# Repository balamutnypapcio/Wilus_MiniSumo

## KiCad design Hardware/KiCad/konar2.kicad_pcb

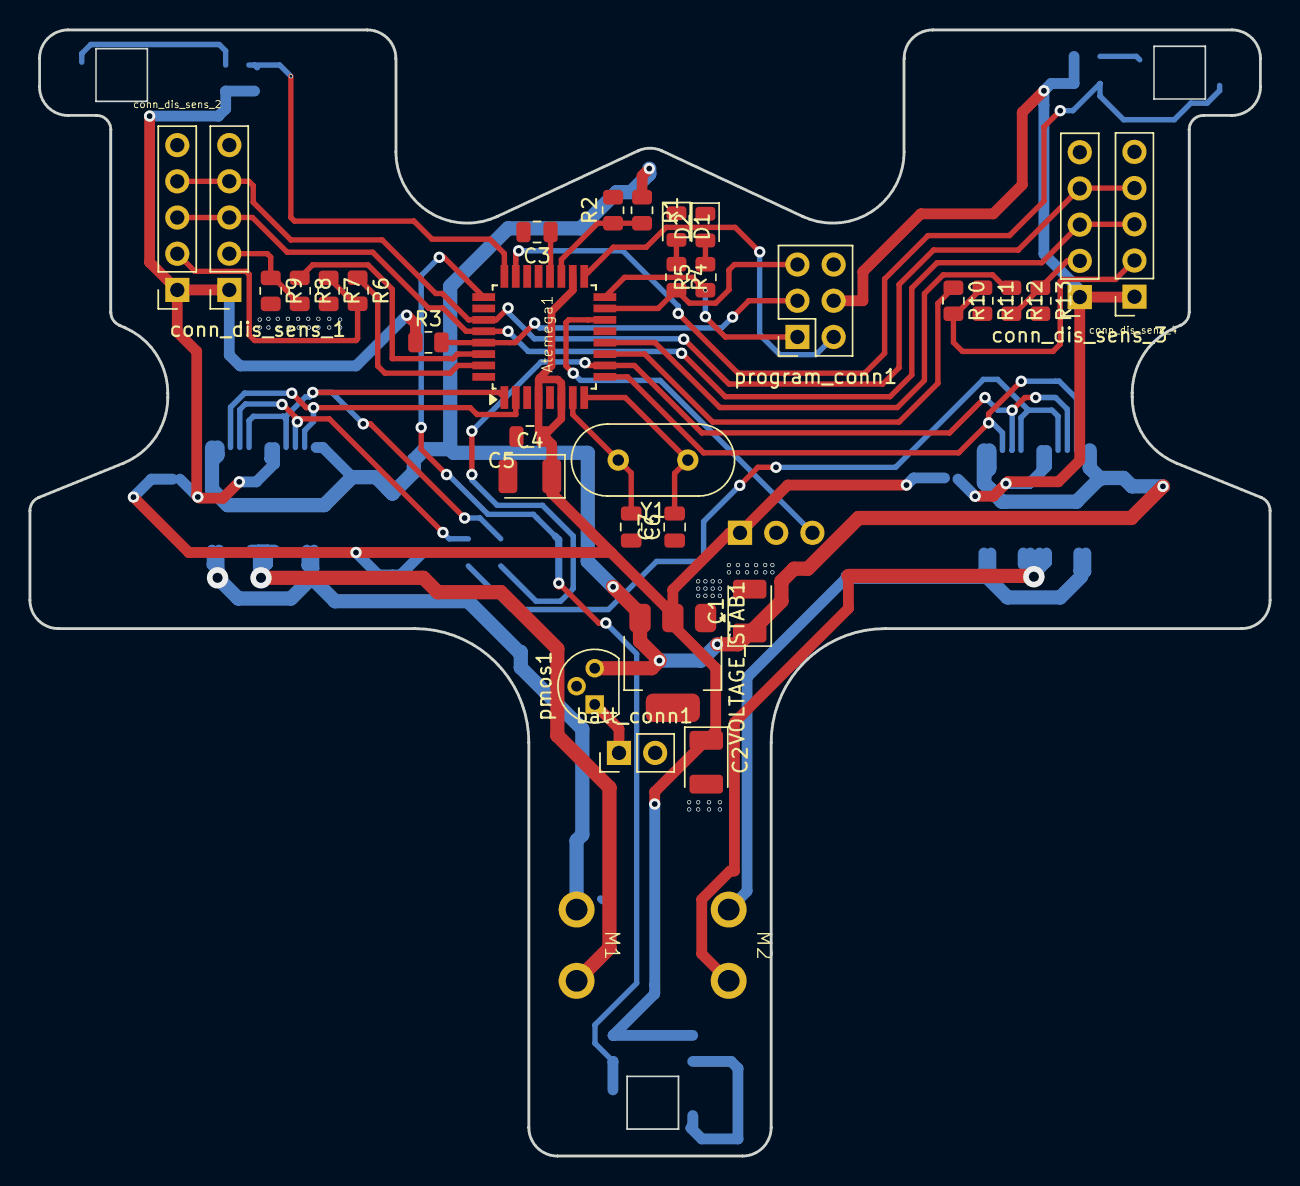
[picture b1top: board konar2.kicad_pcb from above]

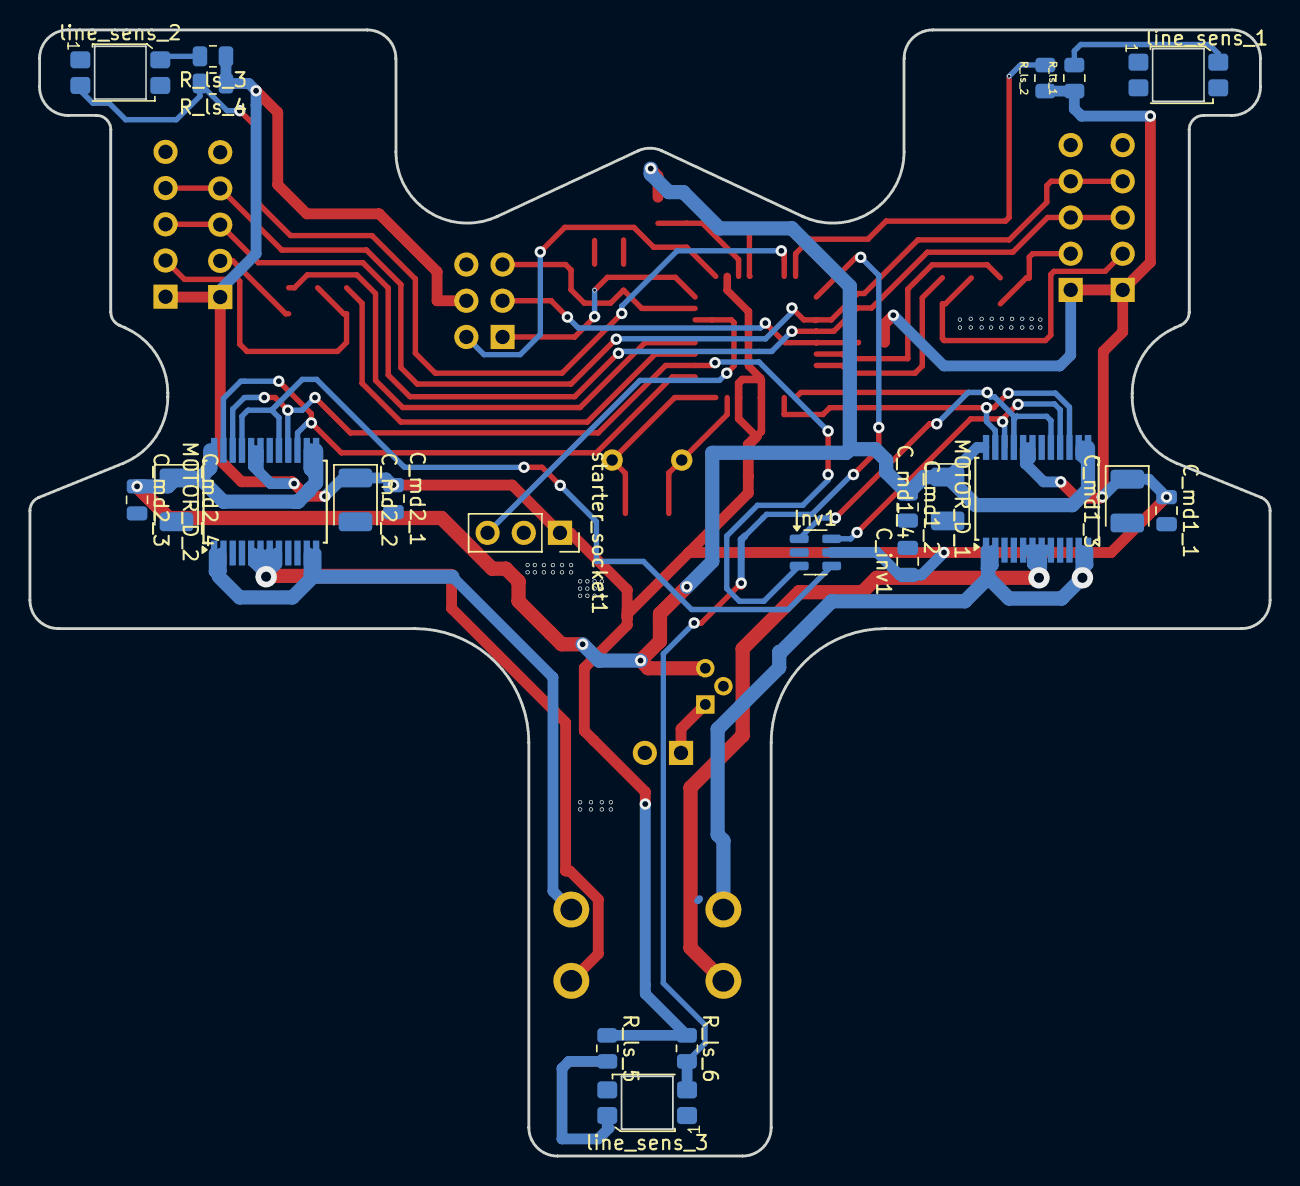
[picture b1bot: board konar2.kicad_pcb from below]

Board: 2 copper layers, 87.0 x 79.0 mm, 56 parts (22 on the bottom side), 41 nets.

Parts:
Atemega1: ATmega328P-A; TQFP-32_7x7mm_P0.8mm
C1, C2, C4: 10u; CP_EIA-3528-12_Kemet-T
C3, C5: 100n; C_0805_2012Metric
C6, C7: 22p; C_0805_2012Metric
C_inv1: 100n; C_0805_2012Metric
C_md1_1, C_md1_2, C_md2_1, C_md2_3: 100n; C_0805_2012Metric
C_md1_3, C_md1_4, C_md2_2, C_md2_4: 10u; CP_EIA-3528-12_Kemet-T
D1, D2: LED; LED_0805_2012Metric
Inv1: SN74LVC2G14DBV; SOT-23-6
M1, M2: Motor
MOTOR_D_1, MOTOR_D_2: TB6612FNG; SSOP-24_5.3x8.2mm_P0.65mm
R1, R2: 10K; R_0805_2012Metric
R3: 10k; R_0805_2012Metric
R4, R5, R6, R8, R10, R12: 1k; R_0805_2012Metric
R7, R9, R11, R13: 2k; R_0805_2012Metric
R_ls_1, R_ls_3, R_ls_5: 200R; R_0805_2012Metric
R_ls_2, R_ls_4, R_ls_6: 10k; R_0805_2012Metric
VOLTAGE_STAB1: LM1117DT-5.0; SOT-223
Y1: Crystal; Crystal_HC49-4H_Vertical
batt_conn1: Conn_01x02_Pin; PinHeader_1x02_P2.54mm_Vertical
conn_dis_sens_1, conn_dis_sens_2, conn_dis_sens_3, conn_dis_sens_4: Conn_01x05_Socket; PinSocket_1x05_P2.54mm_Vertical
line_sens_1, line_sens_2, line_sens_3: ITR8307; Everlight_ITR8307
pmos1: PMOS; TO-92L
program_conn1: AFA01-S06FCC-00; PinSocket_2x03_P2.54mm_Vertical
starter_socket1: Conn_01x03_Socket; PinSocket_1x03_P2.54mm_Vertical

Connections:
+5V: Atemega1.4 (VCC), Atemega1.6 (VCC), Atemega1.18 (AVCC), C2.1, C4.1, C5.1, C_inv1.1, C_md1_1.1, C_md1_3.1, C_md2_1.1, C_md2_2.1, Inv1.5 (V_{CC}), MOTOR_D_1.19 (STBY), MOTOR_D_1.20 (VCC), MOTOR_D_2.19 (STBY), MOTOR_D_2.20 (VCC), R3.1, R_ls_1.1, R_ls_2.1, R_ls_3.1, R_ls_4.1, R_ls_5.1, R_ls_6.1, VOLTAGE_STAB1.2 (VO), conn_dis_sens_1.1, conn_dis_sens_2.1, conn_dis_sens_3.1, conn_dis_sens_4.1, program_conn1.4, starter_socket1.1
+BATT: C1.1, C_md1_2.1, C_md1_4.1, C_md2_3.1, C_md2_4.1, MOTOR_D_1.13 (VM2), MOTOR_D_1.14 (VM3), MOTOR_D_1.24 (VM1), MOTOR_D_2.13 (VM2), MOTOR_D_2.14 (VM3), MOTOR_D_2.24 (VM1), R1.1, VOLTAGE_STAB1.3 (VI), pmos1.3 (S)
/Motor driver 1/a_2: Inv1.6 (1Y), MOTOR_D_1.16 (BIN2), MOTOR_D_1.22 (AIN2)
/Motor driver 1/ao_1: M1.1, MOTOR_D_1.1 (AO1), MOTOR_D_1.2 (AO1), MOTOR_D_1.11 (BO1), MOTOR_D_1.12 (BO1)
/Motor driver 1/ao_2: M1.2, MOTOR_D_1.5 (AO2), MOTOR_D_1.6 (AO2), MOTOR_D_1.7 (BO2), MOTOR_D_1.8 (BO2)
/Motor driver 1/pwm_1: Atemega1.2 (PD5), MOTOR_D_1.15 (PWMB), MOTOR_D_1.23 (PWMA)
/SCL: Atemega1.28 (PC5), conn_dis_sens_1.3, conn_dis_sens_2.3, conn_dis_sens_3.3, conn_dis_sens_4.3
/SDA: Atemega1.27 (PC4), conn_dis_sens_1.4, conn_dis_sens_2.4, conn_dis_sens_3.4, conn_dis_sens_4.4
/XSHUT1: R8.2, R9.1, conn_dis_sens_1.2
/XSHUT2: R6.2, R7.1, conn_dis_sens_2.2
/XSHUT3: R12.2, R13.1, conn_dis_sens_3.2
/XSHUT4: R10.2, R11.1, conn_dis_sens_4.2
/atemega/ADC7: Atemega1.19 (ADC6), R1.2, R2.1
/atemega/AREF: Atemega1.20 (AREF), C3.1
/atemega/MISO: Atemega1.16 (PB4), R5.1, program_conn1.1
/atemega/MISO_R: D2.2 (A), R5.2
/atemega/MOSI: Atemega1.15 (PB3), R4.1, program_conn1.5
/atemega/MOSI_R: D1.2 (A), R4.2
/atemega/Motor_speed_2: Atemega1.9 (PD6), MOTOR_D_2.15 (PWMB), MOTOR_D_2.23 (PWMA)
/atemega/RESET: Atemega1.29 (~RESET/PC6), R3.2, program_conn1.3
/atemega/STARTER: Atemega1.14 (PB2), starter_socket1.3
/atemega/XSHUT1: Atemega1.30 (PD1), R8.1
/atemega/XSHUT2: Atemega1.31 (PD2), R6.1
/atemega/XSHUT3: Atemega1.12 (PB0), R12.1
/atemega/XSHUT4: Atemega1.11 (PD8), R10.1
/atemega/clock: Atemega1.17 (PB5), program_conn1.2
/atemega/line_sensor_1: Atemega1.24 (PC1), R_ls_2.2, line_sens_1.3 (C)
/atemega/line_sensor_2: Atemega1.23 (PC0), R_ls_4.2, line_sens_2.3 (C)
/atemega/line_sensor_3: Atemega1.25 (PC2), R_ls_6.2, line_sens_3.3 (C)
/atemega/quartz_c1: Atemega1.7 (XTAL1/PB6), C6.2, Y1.2
/atemega/quartz_c2: Atemega1.8 (XTAL2/PB7), C7.1, Y1.1
/inverter/~B_DIR: Inv1.4 (2Y), MOTOR_D_2.17 (BIN1), MOTOR_D_2.21 (AIN1)
/motor driver 2/motor_1: M2.1, MOTOR_D_2.1 (AO1), MOTOR_D_2.2 (AO1), MOTOR_D_2.11 (BO1), MOTOR_D_2.12 (BO1)
/motor driver 2/motor_2: M2.2, MOTOR_D_2.5 (AO2), MOTOR_D_2.6 (AO2), MOTOR_D_2.7 (BO2), MOTOR_D_2.8 (BO2)
/motor_dirr_A_inv: Atemega1.1 (PD4), Inv1.1 (1A), MOTOR_D_1.17 (BIN1), MOTOR_D_1.21 (AIN1)
/motor_dirr_B_inv: Atemega1.10 (PD7), Inv1.3 (2A), MOTOR_D_2.16 (BIN2), MOTOR_D_2.22 (AIN2)
/voltage/D_PMOS: batt_conn1.1, pmos1.1 (D)
GND: Atemega1.3 (GND), Atemega1.5 (GND), Atemega1.21 (GND), C1.2, C2.2, C3.2, C4.2, C5.2, C6.1, C7.2, C_inv1.2, C_md1_1.2, C_md1_2.2, C_md1_3.2, C_md1_4.2, C_md2_1.2, C_md2_2.2, C_md2_3.2, C_md2_4.2, D1.1 (K), D2.1 (K), Inv1.2 (GND), MOTOR_D_1.3 (PGND1), MOTOR_D_1.4 (PGND1), MOTOR_D_1.9 (PGND2), MOTOR_D_1.10 (PGND2), MOTOR_D_1.18 (GND), MOTOR_D_2.3 (PGND1), MOTOR_D_2.4 (PGND1), MOTOR_D_2.9 (PGND2), MOTOR_D_2.10 (PGND2), MOTOR_D_2.18 (GND), R2.2, R7.2, R9.2, R11.2, R13.2, VOLTAGE_STAB1.1 (GND), batt_conn1.2, conn_dis_sens_1.5, conn_dis_sens_2.5, conn_dis_sens_3.5, conn_dis_sens_4.5, line_sens_1.1 (K), line_sens_1.4 (E), line_sens_2.1 (K), line_sens_2.4 (E), line_sens_3.1 (K), line_sens_3.4 (E), pmos1.2 (G), program_conn1.6, starter_socket1.2
unnamed: R_ls_1.2, line_sens_1.2 (A)
unnamed: R_ls_3.2, line_sens_2.2 (A)
unnamed: R_ls_5.2, line_sens_3.2 (A)

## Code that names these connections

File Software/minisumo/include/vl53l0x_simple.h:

#ifndef VL53L0X_SIMPLE_H
#define VL53L0X_SIMPLE_H

#include <avr/io.h>
#include <stdint.h>

// XSHUT piny
#define XSHUT1 PD0 // left left
#define XSHUT2 PD1 //left front
#define XSHUT3 PB0 // left left
#define XSHUT4 PD7 // right right

// Nowe adresy, bo na start kazdy ToF ma adres 0x29
#define ADDR1 0x30
#define ADDR2 0x31
#define ADDR3 0x32
#define ADDR4 0x33

void vl53l0x_init(void);
uint16_t vl53l0x_read_mm(void);
void vl53l0x_set_address(uint8_t new_addr);
uint16_t read_sensor(uint8_t addr);

#endif

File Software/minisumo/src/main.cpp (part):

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#define F_CPU 10000000UL // 10MHz

// Definicje pinów LED
#define LED_2 PB4
#define LED_1 PB3

// Adresy czujników ToF (po zmianie adresów przez XSHUT)
uint8_t sensor_addrs[4] = {ADDR1, ADDR2, ADDR3, ADDR4};
// Piny XSHUT dla każdego czujnika
uint8_t xshut_pins[4] = {XSHUT1, XSHUT2, XSHUT3, XSHUT4};
// Tablica na ostatnie odczyty odległości
uint16_t distances[4] = {0, 0, 0, 0};
// Tablica informująca, które czujniki są aktywne
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
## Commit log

2025-04-22 hardware and basic software
2025-04-22 loaded project on computer
2025-04-22 vl53l0x workinng
2025-05-13 change to pinout of atemega for PWM Motor 1
2025-05-13 working motors controll and line sensors
2025-05-23 3 tofs work parallel by I2C
2025-06-10 dokumentacja
